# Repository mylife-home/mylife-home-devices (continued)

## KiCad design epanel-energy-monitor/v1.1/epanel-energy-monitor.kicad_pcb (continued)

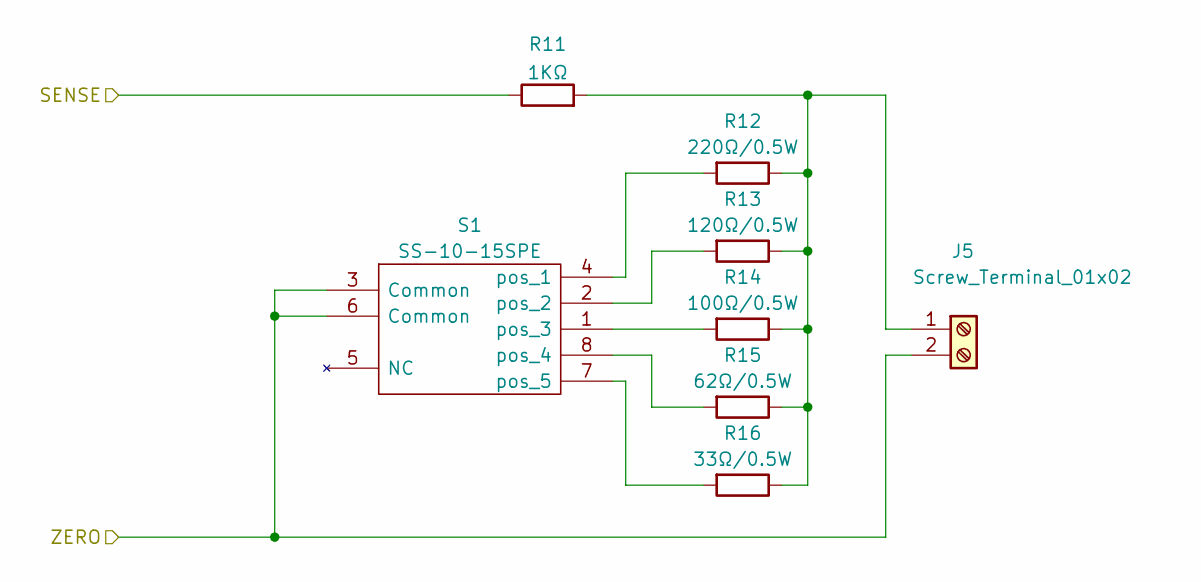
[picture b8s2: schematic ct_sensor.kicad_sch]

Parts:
J5: Screw_Terminal_01x02; RS PRO Terminal Small x2
R11: 1KΩ; R_0603_1608Metric; LCSC C21190
R12: 220Ω/0.5W; R_0805_2012Metric; LCSC C966130
R13: 120Ω/0.5W; R_0805_2012Metric; LCSC C543533
R14: 100Ω/0.5W; R_0805_2012Metric; LCSC C417003
R15: 62Ω/0.5W; R_0805_2012Metric; LCSC C560547
R16: 33Ω/0.5W; R_0805_2012Metric; LCSC C560522
S1: SS-10-15SPE; RS PRO SS-10-15SPE; Manufacturer_Part_Number SS-10-15SPE

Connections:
/CT1: R11.1; also elsewhere on the board
/CT Sensor 1/ZERO: J5.2, S1.3 (Common), S1.6 (Common); also elsewhere on the board
unnamed: J5.1, R11.2, R12.1, R13.1, R14.1, R15.1, R16.1
unnamed: R12.2, S1.4 (pos_1)
unnamed: R13.2, S1.2 (pos_2)
unnamed: R14.2, S1.1 (pos_3)
unnamed: R15.2, S1.8 (pos_4)
unnamed: R16.2, S1.7 (pos_5)

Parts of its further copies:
J6, J7, J8, J9, J10, J11, J12, J13, J14, J15, J16, J17, J18, J19: Screw_Terminal_01x02; RS PRO Terminal Small x2
R17, R23, R29, R35, R41, R47, R53, R59, R65, R71, R77, R83, R89, R95: 1KΩ; R_0603_1608Metric; LCSC C21190
R18, R24, R30, R36, R42, R48, R54, R60, R66, R72, R78, R84, R90, R96: 220Ω/0.5W; R_0805_2012Metric; LCSC C966130
R19, R25, R31, R37, R43, R49, R55, R61, R67, R73, R79, R85, R91, R97: 120Ω/0.5W; R_0805_2012Metric; LCSC C543533
R20, R26, R32, R38, R44, R50, R56, R62, R68, R74, R80, R86, R92, R98: 100Ω/0.5W; R_0805_2012Metric; LCSC C417003
R21, R27, R33, R39, R45, R51, R57, R63, R69, R75, R81, R87, R93, R99: 62Ω/0.5W; R_0805_2012Metric; LCSC C560547
R22, R28, R34, R40, R46, R52, R58, R64, R70, R76, R82, R88, R94, R100: 33Ω/0.5W; R_0805_2012Metric; LCSC C560522
S2, S3, S4, S5, S6, S7, S8, S9, S10, S11, S12, S13, S14, S15: SS-10-15SPE; RS PRO SS-10-15SPE; Manufacturer_Part_Number SS-10-15SPE

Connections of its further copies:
/CT2: R17.1; also elsewhere on the board
/CT3: R23.1; also elsewhere on the board
/CT4: R29.1; also elsewhere on the board
/CT5: R35.1; also elsewhere on the board
/CT6: R41.1; also elsewhere on the board
/CT7: R47.1; also elsewhere on the board
/CT8: R53.1; also elsewhere on the board
/CT9: R59.1; also elsewhere on the board
/CT10: R65.1; also elsewhere on the board
/CT11: R71.1; also elsewhere on the board
/CT12: R77.1; also elsewhere on the board
/CT13: R83.1; also elsewhere on the board
/CT14: R89.1; also elsewhere on the board
/CT15: R95.1; also elsewhere on the board
/CT Sensor 1/ZERO: J6.2, J7.2, J8.2, J9.2, J10.2, J11.2, J12.2, J13.2, J14.2, J15.2, J16.2, J17.2, J18.2, J19.2, S2.3 (Common), S2.6 (Common), S3.3 (Common), S3.6 (Common), S4.3 (Common), S4.6 (Common), S5.3 (Common), S5.6 (Common), S6.3 (Common), S6.6 (Common), S7.3 (Common), S7.6 (Common), S8.3 (Common), S8.6 (Common), S9.3 (Common), S9.6 (Common), S10.3 (Common), S10.6 (Common), S11.3 (Common), S11.6 (Common), S12.3 (Common), S12.6 (Common), S13.3 (Common), S13.6 (Common), S14.3 (Common), S14.6 (Common), S15.3 (Common), S15.6 (Common); also elsewhere on the board
unnamed: J6.1, R17.2, R18.1, R19.1, R20.1, R21.1, R22.1
unnamed: J7.1, R23.2, R24.1, R25.1, R26.1, R27.1, R28.1
unnamed: J8.1, R29.2, R30.1, R31.1, R32.1, R33.1, R34.1
unnamed: J9.1, R35.2, R36.1, R37.1, R38.1, R39.1, R40.1
unnamed: J10.1, R41.2, R42.1, R43.1, R44.1, R45.1, R46.1
unnamed: J11.1, R47.2, R48.1, R49.1, R50.1, R51.1, R52.1
unnamed: J12.1, R53.2, R54.1, R55.1, R56.1, R57.1, R58.1
unnamed: J13.1, R59.2, R60.1, R61.1, R62.1, R63.1, R64.1
unnamed: J14.1, R65.2, R66.1, R67.1, R68.1, R69.1, R70.1
unnamed: J15.1, R71.2, R72.1, R73.1, R74.1, R75.1, R76.1
unnamed: J16.1, R77.2, R78.1, R79.1, R80.1, R81.1, R82.1
unnamed: J17.1, R83.2, R84.1, R85.1, R86.1, R87.1, R88.1
unnamed: J18.1, R89.2, R90.1, R91.1, R92.1, R93.1, R94.1
unnamed: J19.1, R95.2, R96.1, R97.1, R98.1, R99.1, R100.1
unnamed: R18.2, S2.4 (pos_1)
unnamed: R19.2, S2.2 (pos_2)
unnamed: R20.2, S2.1 (pos_3)
unnamed: R21.2, S2.8 (pos_4)
unnamed: R22.2, S2.7 (pos_5)
unnamed: R24.2, S3.4 (pos_1)
unnamed: R25.2, S3.2 (pos_2)
unnamed: R26.2, S3.1 (pos_3)
unnamed: R27.2, S3.8 (pos_4)
unnamed: R28.2, S3.7 (pos_5)
unnamed: R30.2, S4.4 (pos_1)
unnamed: R31.2, S4.2 (pos_2)
unnamed: R32.2, S4.1 (pos_3)
unnamed: R33.2, S4.8 (pos_4)
unnamed: R34.2, S4.7 (pos_5)
unnamed: R36.2, S5.4 (pos_1)
unnamed: R37.2, S5.2 (pos_2)
unnamed: R38.2, S5.1 (pos_3)
unnamed: R39.2, S5.8 (pos_4)
unnamed: R40.2, S5.7 (pos_5)
unnamed: R42.2, S6.4 (pos_1)
unnamed: R43.2, S6.2 (pos_2)
unnamed: R44.2, S6.1 (pos_3)
unnamed: R45.2, S6.8 (pos_4)
unnamed: R46.2, S6.7 (pos_5)
unnamed: R48.2, S7.4 (pos_1)
unnamed: R49.2, S7.2 (pos_2)
unnamed: R50.2, S7.1 (pos_3)
unnamed: R51.2, S7.8 (pos_4)
unnamed: R52.2, S7.7 (pos_5)
unnamed: R54.2, S8.4 (pos_1)
unnamed: R55.2, S8.2 (pos_2)
unnamed: R56.2, S8.1 (pos_3)
unnamed: R57.2, S8.8 (pos_4)
unnamed: R58.2, S8.7 (pos_5)
unnamed: R60.2, S9.4 (pos_1)
unnamed: R61.2, S9.2 (pos_2)
unnamed: R62.2, S9.1 (pos_3)
unnamed: R63.2, S9.8 (pos_4)
unnamed: R64.2, S9.7 (pos_5)
unnamed: R66.2, S10.4 (pos_1)
unnamed: R67.2, S10.2 (pos_2)
unnamed: R68.2, S10.1 (pos_3)
unnamed: R69.2, S10.8 (pos_4)
unnamed: R70.2, S10.7 (pos_5)
unnamed: R72.2, S11.4 (pos_1)
unnamed: R73.2, S11.2 (pos_2)
unnamed: R74.2, S11.1 (pos_3)
unnamed: R75.2, S11.8 (pos_4)
unnamed: R76.2, S11.7 (pos_5)
unnamed: R78.2, S12.4 (pos_1)
unnamed: R79.2, S12.2 (pos_2)
unnamed: R80.2, S12.1 (pos_3)
unnamed: R81.2, S12.8 (pos_4)
unnamed: R82.2, S12.7 (pos_5)
unnamed: R84.2, S13.4 (pos_1)
unnamed: R85.2, S13.2 (pos_2)
unnamed: R86.2, S13.1 (pos_3)
unnamed: R87.2, S13.8 (pos_4)
unnamed: R88.2, S13.7 (pos_5)
unnamed: R90.2, S14.4 (pos_1)
unnamed: R91.2, S14.2 (pos_2)
unnamed: R92.2, S14.1 (pos_3)
unnamed: R93.2, S14.8 (pos_4)
unnamed: R94.2, S14.7 (pos_5)
unnamed: R96.2, S15.4 (pos_1)
unnamed: R97.2, S15.2 (pos_2)
unnamed: R98.2, S15.1 (pos_3)
unnamed: R99.2, S15.8 (pos_4)
unnamed: R100.2, S15.7 (pos_5)

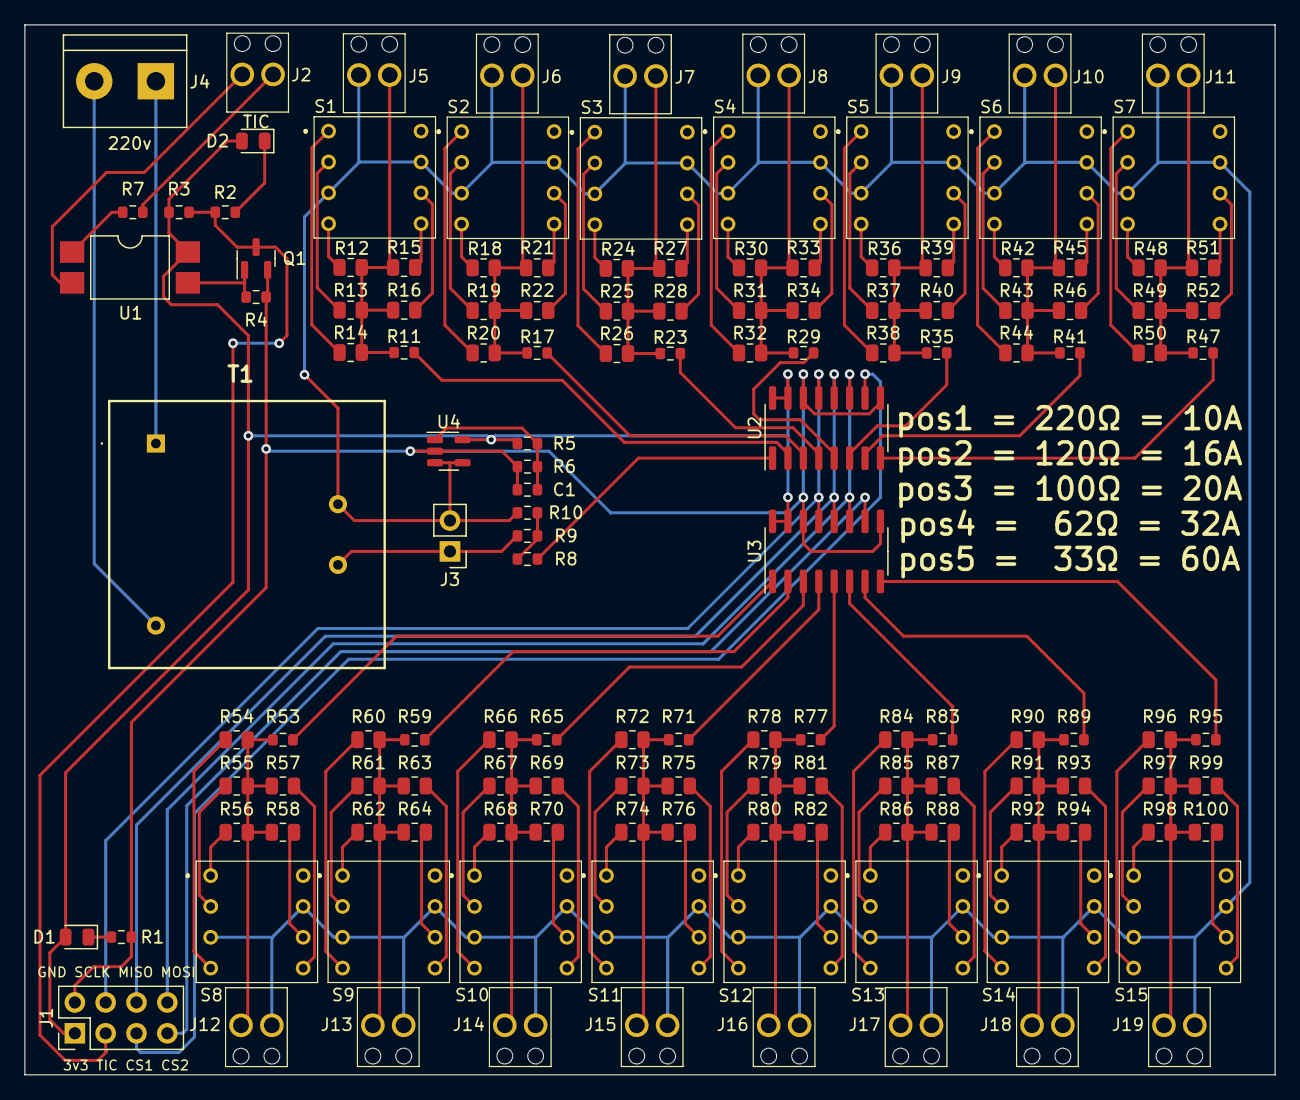
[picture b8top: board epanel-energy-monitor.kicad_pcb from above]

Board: 2 copper layers, 103.0 x 86.5 mm, 143 parts (0 on the bottom side), 126 nets.

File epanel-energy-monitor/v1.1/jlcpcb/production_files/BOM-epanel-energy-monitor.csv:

Comment,Designator,Footprint,LCSC
LTV-814,U1,SMDIP-4_W9.53mm,C125118
1uF/6V,C1,R_0603_1608Metric,C15849
MCP3208,"U2,U3",SOIC-16_3.9x9.9mm_P1.27mm,C16939
1KΩ,"R1,R11,R17,R2,R23,R29,R35,R41,R47,R53,R59,R65,R71,R77,R8,R83,R89,R95",R_0603_1608Metric,C21190
12KΩ,"R10,R5,R6",R_0603_1608Metric,C22790
220Ω,R7,R_0603_1608Metric,C22962
LED,"D1,D2",D_0805_2012Metric,C2297
3.3KΩ,R4,R_0603_1608Metric,C22978
100KΩ,R9,R_0603_1608Metric,C25803
10KΩ,R3,R_0603_1608Metric,C25804
BSS138,Q1,SOT-23,C2938375
100Ω/0.5W,"R14,R20,R26,R32,R38,R44,R50,R56,R62,R68,R74,R80,R86,R92,R98",R_0805_2012Metric,C417003
120Ω/0.5W,"R13,R19,R25,R31,R37,R43,R49,R55,R61,R67,R73,R79,R85,R91,R97",R_0805_2012Metric,C543533
33Ω/0.5W,"R100,R16,R22,R28,R34,R40,R46,R52,R58,R64,R70,R76,R82,R88,R94",R_0805_2012Metric,C560522
62Ω/0.5W,"R15,R21,R27,R33,R39,R45,R51,R57,R63,R69,R75,R81,R87,R93,R99",R_0805_2012Metric,C560547
LMV321,U4,SOT-23-5,C7972
220Ω/0.5W,"R12,R18,R24,R30,R36,R42,R48,R54,R60,R66,R72,R78,R84,R90,R96",R_0805_2012Metric,C966130
SS-10-15SPE,S15,RS PRO SS-10-15SPE,
Screw_Terminal_01x02,J15,RS PRO Terminal Small x2,
SS-10-15SPE,S12,RS PRO SS-10-15SPE,
SS-10-15SPE,S11,RS PRO SS-10-15SPE,
Screw_Terminal_01x02,J5,RS PRO Terminal Small x2,
Screw_Terminal_01x02,J6,RS PRO Terminal Small x2,
SS-10-15SPE,S6,RS PRO SS-10-15SPE,
Screw_Terminal_01x02,J2,RS PRO Terminal Small x2,
Screw_Terminal_01x02,J7,RS PRO Terminal Small x2,
SS-10-15SPE,S8,RS PRO SS-10-15SPE,
Screw_Terminal_01x02,J11,RS PRO Terminal Small x2,
SS-10-15SPE,S1,RS PRO SS-10-15SPE,
SS-10-15SPE,S5,RS PRO SS-10-15SPE,
Conn_02x04_Odd_Even,J1,PinHeader_2x04_P2.54mm_Vertical,
SS-10-15SPE,S3,RS PRO SS-10-15SPE,
SS-10-15SPE,S4,RS PRO SS-10-15SPE,
Screw_Terminal_01x02,J8,RS PRO Terminal Small x2,
Screw_Terminal_01x02,J9,RS PRO Terminal Small x2,
SS-10-15SPE,S7,RS PRO SS-10-15SPE,
SS-10-15SPE,S2,RS PRO SS-10-15SPE,
Screw_Terminal_01x02,J14,RS PRO Terminal Small x2,
Screw_Terminal_01x02,J16,RS PRO Terminal Small x2,
SS-10-15SPE,S13,RS PRO SS-10-15SPE,
SS-10-15SPE,S9,RS PRO SS-10-15SPE,
Conn_01x02_Male,J3,PinHeader_1x02_P2.54mm_Vertical,
Screw_Terminal_01x02,J4,TerminalBlock_bornier-2_P5.08mm,
SS-10-15SPE,S10,RS PRO SS-10-15SPE,
Screw_Terminal_01x02,J10,RS PRO Terminal Small x2,
Screw_Terminal_01x02,J17,RS PRO Terminal Small x2,
Screw_Terminal_01x02,J19,RS PRO Terminal Small x2,
Screw_Terminal_01x02,J12,RS PRO Terminal Small x2,
Screw_Terminal_01x02,J18,RS PRO Terminal Small x2,
230V - 6V,T1,RS PRO Transfo 6V 0.35VA,
Screw_Terminal_01x02,J13,RS PRO Terminal Small x2,
SS-10-15SPE,S14,RS PRO SS-10-15SPE,

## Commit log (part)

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2022-12-31 cleanup
2022-12-31 add switch
2022-12-31 restore switch drill diameter
2022-12-31 add small terminal footprint
2022-12-31 update TODO
2022-12-31 rotary switch
2023-01-01 update schematic
2023-01-01 update notes
2023-01-01 base pcb
2023-01-01 add borders
2023-01-01 wip tests
2023-01-01 update note
2023-01-01 update footprint
2023-01-01 wip tests pcb
2023-01-01 add CNMB pdf
2023-01-02 wip split controller
2023-01-02 schematic remove esp
2023-01-02 wip controller
2023-01-02 controller schematic
2023-01-02 update controller schematic
2023-01-02 enery monitor schematic
2023-01-02 wip pcb placement
2023-01-02 wip energy pcb
2023-01-02 wip pcb
2023-01-02 fix annotations
2023-01-02 pcb beta
2023-01-02 wip DRC
2023-01-02 add info
2023-01-03 fabrication files
2023-01-03 controller pcb placement
2023-01-03 controller pcb
2023-01-08 update 3dview
2023-01-08 add 3dview
2023-01-08 oops
2023-01-14 add test notes
2023-01-15 garden box presse etoupes
2023-02-04 update controller
2023-02-18 init v1.1
2023-02-18 fix pinouts
2023-02-18 wip fix pcb
2023-02-18 pcb placement
2023-02-18 wip pcb naming
2023-02-18 fix pcb
2023-02-18 update prod files
2023-02-18 add images
2023-02-19 rgb-box skeleton
2023-02-19 update ref spot
2023-02-20 update README + garden only
2023-02-21 convert to v7
2023-02-22 update rgb garden box
2023-02-24 update rgb box notes
2023-02-24 update organization + spot notes
2023-02-24 cosmetic
2023-02-25 update rgb spot notes
2023-02-25 add footprints
2023-02-25 fix layer + cut
2023-02-25 wip schematic
2023-02-25 pcb OK
2023-02-25 add schematic
2023-02-25 fix footprint
2023-02-25 add production files
2023-02-28 update PCB R200 to 220
2023-03-09 mark GPIO0 (strapping pin) as unconnected on ESP32-POE
2023-03-09 rgb-garden-box wip schematic
2023-03-10 enclosing box layout
2023-03-10 update footprints for ESP32-POE
2023-03-10 DRC OK
2023-03-13 update presse etoupes
2023-03-18 switch IRLZ44N to TO220
2023-03-18 production files
2023-03-21 add pictures
2023-03-24 update pictures
2023-03-26 update bed smart plug
2023-04-07 add wiring
2023-04-22 add picture
2023-05-02 update list
2023-05-02 add garden box pictures
2023-05-02 test
2023-05-02 fix md layout
2023-05-05 Add potential projects
2023-05-07 add R&D garage door
2023-05-07 typo
2023-05-07 fix pictures layout
2023-05-10 update garage door driver readme
2023-05-14 energy monitor pics
2023-05-14 garage door add pics
2023-05-15 add energy pictures
2023-05-17 garage door R&D
2023-05-19 copy/paste schematic
2023-05-19 clean PCB + add edge cuts
2023-05-20 add wemos schematic/footprint library
2023-05-20 wip sch
2023-05-22 add ESP8266 strapping pins
2023-05-22 fix esp8366 used pins
2023-05-22 annotate
2023-05-22 jlcpcb
2023-05-22 ajout ref borniers
2023-06-01 udpate README
2023-06-05 finalize
2023-06-05 add clim data
2023-06-05 add overflow pictures
2023-06-10 add toshiba notes
2023-06-20 add pcb size
2023-07-04 clim driver routing
2023-07-04 jlcpcb stuff
2023-07-04 3dview
2023-09-03 update pictures + notes clim driver
2023-09-07 Add clim-driver data
2023-09-07 Add wifi presence datra
2023-09-07 clim proto picture
2023-09-30 check
2023-09-30 layout
2023-10-16 update bed-smart-plug
2023-11-14 update project version
2023-11-14 proto1 wip schematic
2023-11-15 wip schematics
2023-11-15 update README/schematic
2023-11-15 fix symbols
2023-11-15 add footprint
2023-11-15 Recepteur 433Mhz
2023-11-15 update fusibles
2023-11-15 update heatsink
2023-11-15 jack
2023-11-15 Add DS18b20 ref
2023-11-15 Update C13/C14 plugs
2023-11-16 placement
2023-11-16 routing
2023-11-16 output files
2023-11-16 Add materiel
2023-11-16 Update materiel
2024-01-06 Add proto 1 schematic
2024-01-06 Add pinout
2024-01-06 add notes
2024-01-06 fix table
2024-01-06 cosmtic
2024-01-12 Add connectors stuff
2024-01-14 ajout écrous
2024-01-20 update observations proto 2
2024-01-20 update proto2
2024-01-20 update proto 3
2024-01-20 wip proto 3
2024-01-20 proto 3 wip
2024-01-21 update observations proto 1
2024-01-21 update todos proto3
2024-01-21 update PCB
2024-01-21 jlcpcb output proto3
2024-01-21 rework proto 3 edge cuts
2024-01-21 update pcb borders
2024-01-21 jlcpcb generate
2024-01-21 v1 schematic OK
2024-01-21 note
2024-01-27 wip pcb v1
2024-01-27 place components
2024-01-27 wip placement
2024-01-27 component placement
2024-01-27 wip routing
2024-01-27 generate jlcpcb parts
2024-01-27 jlcpcb order
2024-02-05 add notes v1
2024-03-08 add pic
2024-03-09 pictures + notes
2024-03-10 wip v1.1
2024-03-10 pcb size
2024-03-10 pics
2024-03-10 update moc3021 to available part
2024-03-14 gabarits
2024-03-15 add epanel controller debug ops
2024-03-19 add uart debug result
2024-03-20 update build images
2024-04-12 update remote data
2024-06-20 init rgb-led-inverter
2024-06-20 notes
2024-06-27 add note
2024-12-26 fairy lights
2024-12-26 heat driver skeleton
2024-12-27 update heater driver
2025-01-04 Add design notes
2025-01-04 add alims dimensions
2025-01-13 add notes proto 1
2025-01-18 init schematic
2025-01-19 add connector
2025-01-19 Add V1 skeleton
2025-01-19 fix schematic
2025-01-26 finish schematic + footprints
2025-02-08 Add heatsink
2025-02-09 routing + sign
2025-02-09 wiring
2025-02-09 jlcpcb gen
2025-06-16 materiel
2025-07-23 Add notes for epanelio v1.1
2025-08-23 Ajout doc construction gate-driver
2025-08-23 Ajout notes
2025-08-25 update fairylights
2025-09-14 Change RGB LED inverter status from question to stop
2025-09-14 Change RGB LED inverter status to 'no entry'
2026-02-04 Update README + deco-light
2026-03-08 add gate driver pairing notes
